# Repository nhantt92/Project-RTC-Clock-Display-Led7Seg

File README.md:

# Project-RTC-Clock-Display-Led7Seg
Project-RTC-Clock-Display-Led7Seg

## Hardware

### Image Top

### Image Bot

## Firmware
RTC_FW

## Product

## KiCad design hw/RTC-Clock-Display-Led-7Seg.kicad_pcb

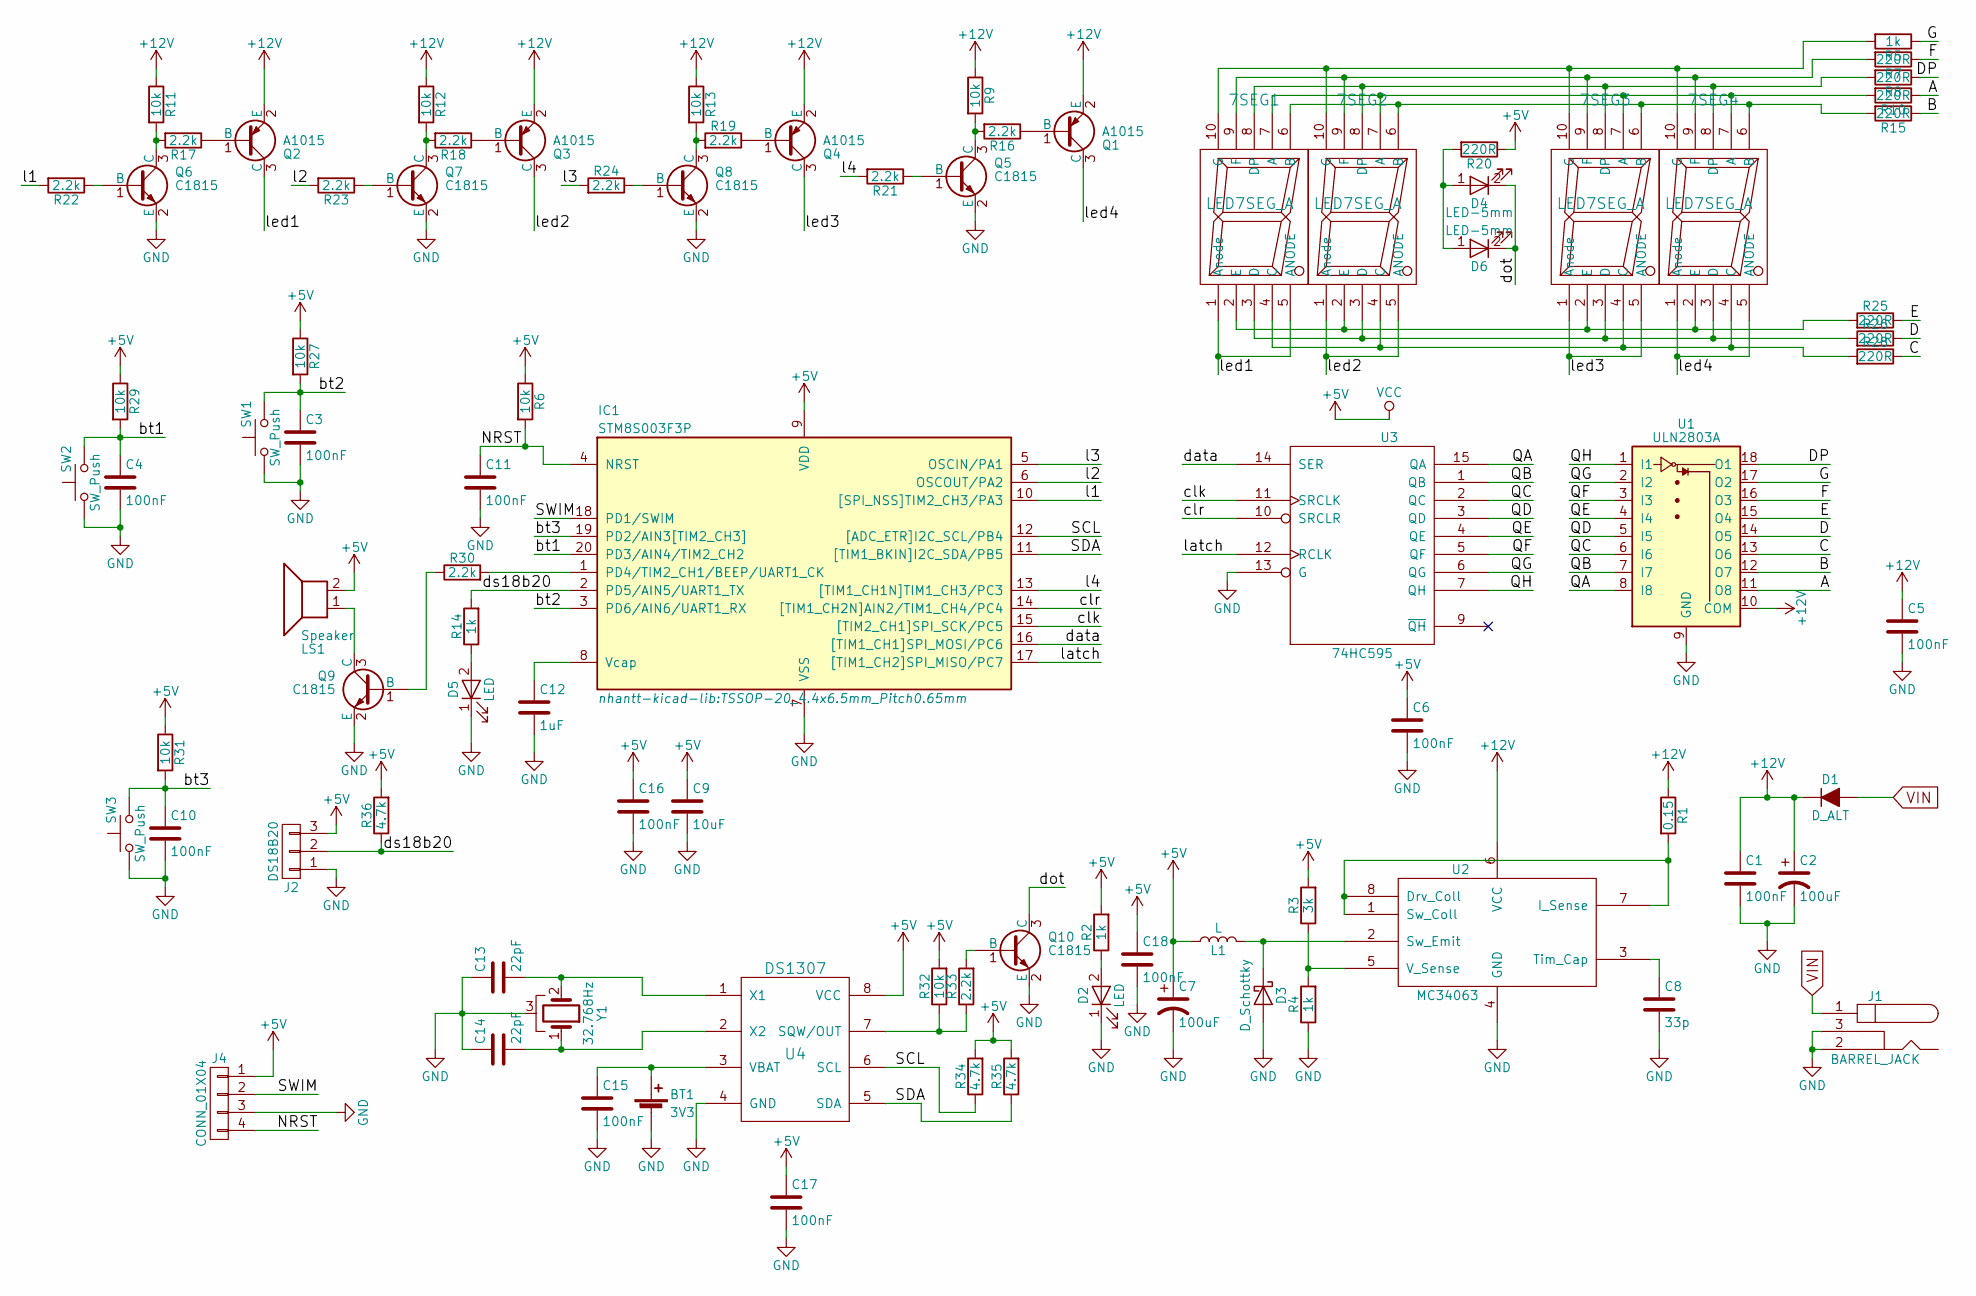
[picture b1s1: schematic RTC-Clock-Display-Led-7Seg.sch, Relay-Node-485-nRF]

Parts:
7SEG1, 7SEG2, 7SEG3, 7SEG4: LED7SEG_A; LED-7SEG-23101BX
BT1: 3V3; BT3V3
C1, C3, C4, C5, C6, C10, C11, C15, C16, C17, C18: 100nF; C_0805_HandSoldering
C2: 100uF; CP_Elec_8x10.5
C7: 100uF; CP_Elec_8x10
C8: 33p; C_0805_HandSoldering
C9: 10uF; C_1206_HandSoldering
C12: 1uF; C_0805_HandSoldering
C13, C14: 22pF; C_0805_HandSoldering
D1: D_ALT; D_SMA_Standard
D2, D5: LED; LED_0805
D3: D_Schottky; D_SMB_Handsoldering
D4, D6: LED-5mm; LED_D5.0mm
IC1: STM8S003F3P; TSSOP-20_4.4x6.5mm_Pitch0.65mm
J1: BARREL_JACK; JACK_DC
J2: DS18B20; TO-92_Inline_Wide
J4: CONN_01X04; Header-4pin-2.54
L1: L; Inductor_5.2x5.8x4.5
LS1: Speaker; Buzzer_12x9.5RM7.6
Q1, Q2, Q3, Q4: A1015; SOT-23
Q5, Q6, Q7, Q8, Q9, Q10: C1815; SOT-23
R1: 0.15; R_1206_HandSoldering
R2, R4, R5, R14: 1k; R_0805_HandSoldering
R3: 3k; R_0805_HandSoldering
R6, R9, R11, R12, R13, R27, R29, R31, R32: 10k; R_0805_HandSoldering
R7, R8, R10, R15, R20, R25, R26, R28: 220R; R_0805_HandSoldering
R16, R17, R18, R19, R21, R22, R23, R24, R30, R33: 2.2k; R_0805_HandSoldering
R34, R35, R36: 4.7k; R_0805_HandSoldering
SW1, SW2, SW3: SW_Push; button_TS-6601V-6
U1: ULN2803A; SOIC-18W_7.5x11.6mm_Pitch1.27mm
U2: MC34063; SOIC-8_3.9x4.9mm_Pitch1.27mm
U3: 74HC595; SOIC-16W_5.3x10.2mm_Pitch1.27mm
U4: DS1307; SOIC-8_3.9x4.9mm_Pitch1.27mm
Y1: 32.768Hz; Crystal_Round_Horizontal_3mm_smd

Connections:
+5V: C6.1, C7.1, C9.1, C16.1, C17.1, C18.1, IC1.9 (VDD), J2.3, J4.1, L1.1, LS1.2, R2.2, R3.2, R6.1, R20.1, R27.1, R29.1, R31.1, R32.2, R34.2, R35.2, R36.2, U3.16 (VCC), U4.8 (VCC)
+12V: C1.1, C2.1, C5.1, D1.1 (K), Q1.2 (E), Q2.2 (E), Q3.2 (E), Q4.2 (E), R1.1, R9.1, R11.1, R12.1, R13.1, U1.10 (COM), U2.6 (VCC)
/A: R10.1, U1.11 (O8)
/B: R15.1, U1.12 (O7)
/C: R28.1, U1.13 (O6)
/D: R26.1, U1.14 (O5)
/DP: R8.1, U1.18 (O1)
/E: R25.1, U1.15 (O4)
/F: R7.1, U1.16 (O3)
/G: R5.1, U1.17 (O2)
/NRST: C11.1, IC1.4 (NRST), J4.4, R6.2
/QA: U1.8 (I8), U3.15 (QA)
/QB: U1.7 (I7), U3.1 (QB)
/QC: U1.6 (I6), U3.2 (QC)
/QD: U1.5 (I5), U3.3 (QD)
/QE: U1.4 (I4), U3.4 (QE)
/QF: U1.3 (I3), U3.5 (QF)
/QG: U1.2 (I2), U3.6 (QG)
/QH: U1.1 (I1), U3.7 (QH)
/SCL: IC1.12 ([ADC_ETR]I2C_SCL/PB4), R34.1, U4.6 (SCL)
/SDA: IC1.11 ([TIM1_BKIN]I2C_SDA/PB5), R35.1, U4.5 (SDA)
/SWIM: IC1.18 (PD1/SWIM), J4.2
/bt1: C4.1, IC1.20 (PD3/AIN4/TIM2_CH2), R29.2, SW2.2
/bt2: C3.1, IC1.3 (PD6/AIN6/UART1_RX), R27.2, SW1.2
/bt3: C10.1, IC1.19 (PD2/AIN3[TIM2_CH3]), R31.2, SW3.2
/clk: IC1.15 ([TIM2_CH1]SPI_SCK/PC5), U3.11 (SRCLK)
/clr: IC1.14 ([TIM1_CH2N]AIN2/TIM1_CH4/PC4), U3.10 (SRCLR)
/data: IC1.16 ([TIM1_CH1]SPI_MOSI/PC6), U3.14 (SER)
/dot: D4.2 (K), D6.2 (K), Q10.3 (C)
/ds18b20: IC1.2 (PD5/AIN5/UART1_TX), J2.2, R14.2, R36.1
/l1: IC1.10 ([SPI_NSS]TIM2_CH3/PA3), R22.2
/l2: IC1.6 (OSCOUT/PA2), R23.2
/l3: IC1.5 (OSCIN/PA1), R24.2
/l4: IC1.13 ([TIM1_CH1N]TIM1_CH3/PC3), R21.2
/latch: IC1.17 ([TIM1_CH2]SPI_MISO/PC7), U3.12 (RCLK)
/led1: 7SEG1.1 (Anode), 7SEG1.5 (ANODE), Q2.3 (C)
/led2: 7SEG2.1 (Anode), 7SEG2.5 (ANODE), Q3.3 (C)
/led3: 7SEG3.1 (Anode), 7SEG3.5 (ANODE), Q4.3 (C)
/led4: 7SEG4.1 (Anode), 7SEG4.5 (ANODE), Q1.3 (C)
GND: BT1.2 (-), C1.2, C2.2, C3.2, C4.2, C5.2, C6.2, C7.2, C8.2, C9.2, C10.2, C11.2, C12.2, C13.1, C14.1, C15.2, C16.2, C17.2, C18.2, D2.1 (K), D3.2 (A), D5.1 (K), IC1.7 (VSS), J1.2, J1.3, J2.1, J4.3, Q5.2 (E), Q6.2 (E), Q7.2 (E), Q8.2 (E), Q9.2 (E), Q10.2 (E), R4.1, SW1.1, SW2.1, SW3.1, U1.9 (GND), U2.4 (GND), U3.8 (GND), U3.13 (G), U4.4 (GND), Y1.3
unnamed: 7SEG1.2 (E), 7SEG2.2 (E), 7SEG3.2 (E), 7SEG4.2 (E), R25.2
unnamed: 7SEG1.3 (D), 7SEG2.3 (D), 7SEG3.3 (D), 7SEG4.3 (D), R26.2
unnamed: 7SEG1.4 (C), 7SEG2.4 (C), 7SEG3.4 (C), 7SEG4.4 (C), R28.2
unnamed: 7SEG1.6 (B), 7SEG2.6 (B), 7SEG3.6 (B), 7SEG4.6 (B), R15.2
unnamed: 7SEG1.7 (A), 7SEG2.7 (A), 7SEG3.7 (A), 7SEG4.7 (A), R10.2
unnamed: 7SEG1.8 (DP), 7SEG2.8 (DP), 7SEG3.8 (DP), 7SEG4.8 (DP), R8.2
unnamed: 7SEG1.9 (F), 7SEG2.9 (F), 7SEG3.9 (F), 7SEG4.9 (F), R7.2
unnamed: 7SEG1.10 (G), 7SEG2.10 (G), 7SEG3.10 (G), 7SEG4.10 (G), R5.2
unnamed: BT1.1 (+), C15.1, U4.3 (VBAT)
unnamed: C8.1, U2.3 (Tim_Cap)
unnamed: C12.1, IC1.8 (Vcap)
unnamed: C13.2, U4.1 (X1), Y1.2
unnamed: C14.2, U4.2 (X2), Y1.1
unnamed: D2.2 (A), R2.1
unnamed: D3.1 (K), L1.2, U2.2 (Sw_Emit)
unnamed: D4.1 (A), D6.1 (A), R20.2
unnamed: D5.2 (A), R14.1
unnamed: IC1.1 (PD4/TIM2_CH1/BEEP/UART1_CK), R30.2
unnamed: LS1.1, Q9.3 (C)
unnamed: Q1.1 (B), R16.1
unnamed: Q2.1 (B), R17.1
unnamed: Q3.1 (B), R18.1
unnamed: Q4.1 (B), R19.1
unnamed: Q5.1 (B), R21.1
unnamed: Q5.3 (C), R9.2, R16.2
unnamed: Q6.1 (B), R22.1
unnamed: Q6.3 (C), R11.2, R17.2
unnamed: Q7.1 (B), R23.1
unnamed: Q7.3 (C), R12.2, R18.2
unnamed: Q8.1 (B), R24.1
unnamed: Q8.3 (C), R13.2, R19.2
unnamed: Q9.1 (B), R30.1
unnamed: Q10.1 (B), R33.2
unnamed: R1.2, U2.1 (Sw_Coll), U2.7 (I_Sense), U2.8 (Drv_Coll)
unnamed: R3.1, R4.2, U2.5 (V_Sense)
unnamed: R32.1, R33.1, U4.7 (SQW/OUT)
VIN: D1.2 (A), J1.1

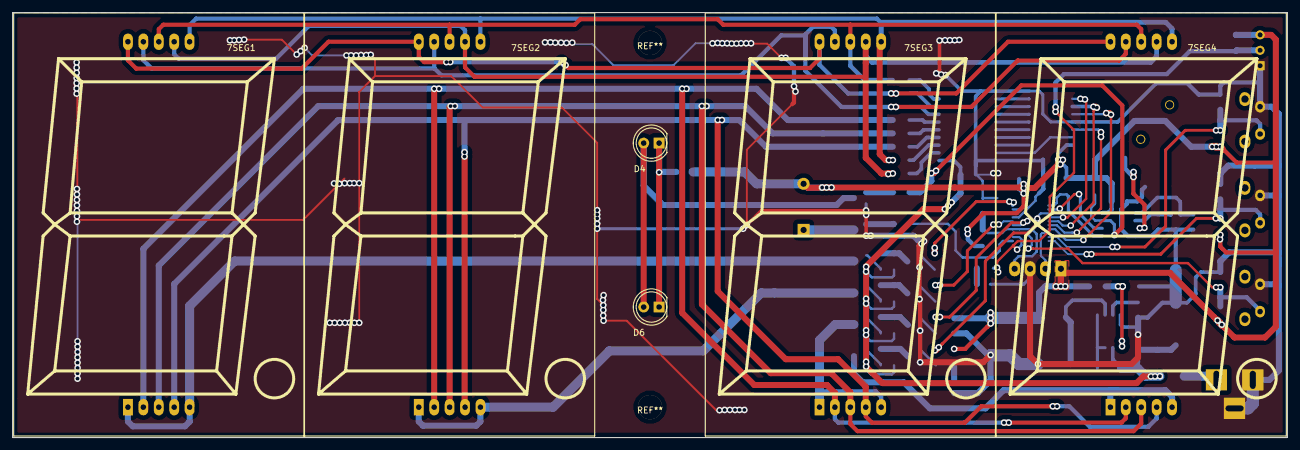
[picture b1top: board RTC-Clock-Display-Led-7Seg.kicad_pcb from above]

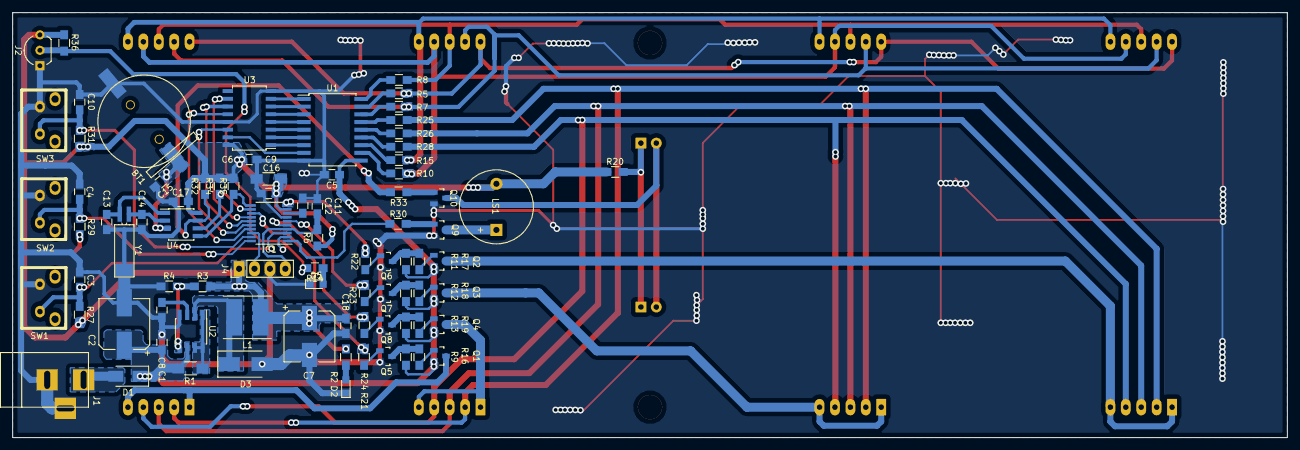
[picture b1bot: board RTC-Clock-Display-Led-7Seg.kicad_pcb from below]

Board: 2 copper layers, 210.0 x 70.0 mm, 89 parts (83 on the bottom side), 77 nets.

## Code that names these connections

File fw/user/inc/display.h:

#ifndef __DISPLAY_H
#define __DISPLAY_H
#include "stm8s.h"
#include "stm8s_gpio.h"

typedef struct
{
	GPIO_TypeDef* portData;
	GPIO_TypeDef* portScan;
	uint8_t data;
	uint8_t clk;
	uint8_t lat;
	uint8_t clr;
	uint8_t led[4];
	uint8_t buffer[4];
}DisplayLed_Struct;

void displayInit(GPIO_TypeDef* portData, GPIO_TypeDef* portScan, uint8_t data, uint8_t clk, uint8_t lat, uint8_t clr, uint8_t led1, uint8_t led2, uint8_t led3, uint8_t led4);
void shiftOut595(uint8_t data);
void latch595(void);
void clear595(void);
void display_test(uint8_t intensy);
void setDigit(uint8_t led, uint8_t bcd);
void screen(uint8_t intensy);

#endif

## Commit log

2018-01-04 add Schematic
2018-01-04 add lib layout
2018-01-05 upload
2018-01-06 complete layout
2018-01-08 complete hw
2018-02-04 init 7seg fw
2018-03-03 display hh:mm ok
2018-03-16 update code
2018-03-17 complete
